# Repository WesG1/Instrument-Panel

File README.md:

# Instrument Panel
Description:
    Digital custom 65 mustang modern insturment panel. Uses six servo motors along with RGB LEDs to display gauge information. Controlled by an ESP32-s2. Motors and warning lights are interfaced through I2C protocall using a PCA9685 controller. Odometer and tripmeter are displayed on an I2C LCD. 
    
    Odo and trip values are stored in an EEPROM chip with a wear leveling algorithm. Odometer value is also stored in a second backup EEPROM. At startup the values of both EEPROMs are read, and if they are different the higher value is set as the current mileage. At shutdown the last stored value and current value for the mileage are compared and the current value is only stored if it is higher than the saved value.

    Each servo motor (execpt voltage) has a deticated sensor. The signals from the oil, temp, and fuel sensors are passed through a calibrated voltage divider to drop them to a level safe for the ESP32 to read. Speed and tach are a digital pulse and are passed through a logic shifter. Voltage is derived by an algorithm and read by a voltage divider from the dash power supply. Volts, oil, temp, and fuel have accompanying warning lights that turn red if the value goes out of a safe range, are off if the value is normal and the headlights are off, and white if the values is normal and the headlights are on. Temp has additionally will turn yellow if the value is too low.

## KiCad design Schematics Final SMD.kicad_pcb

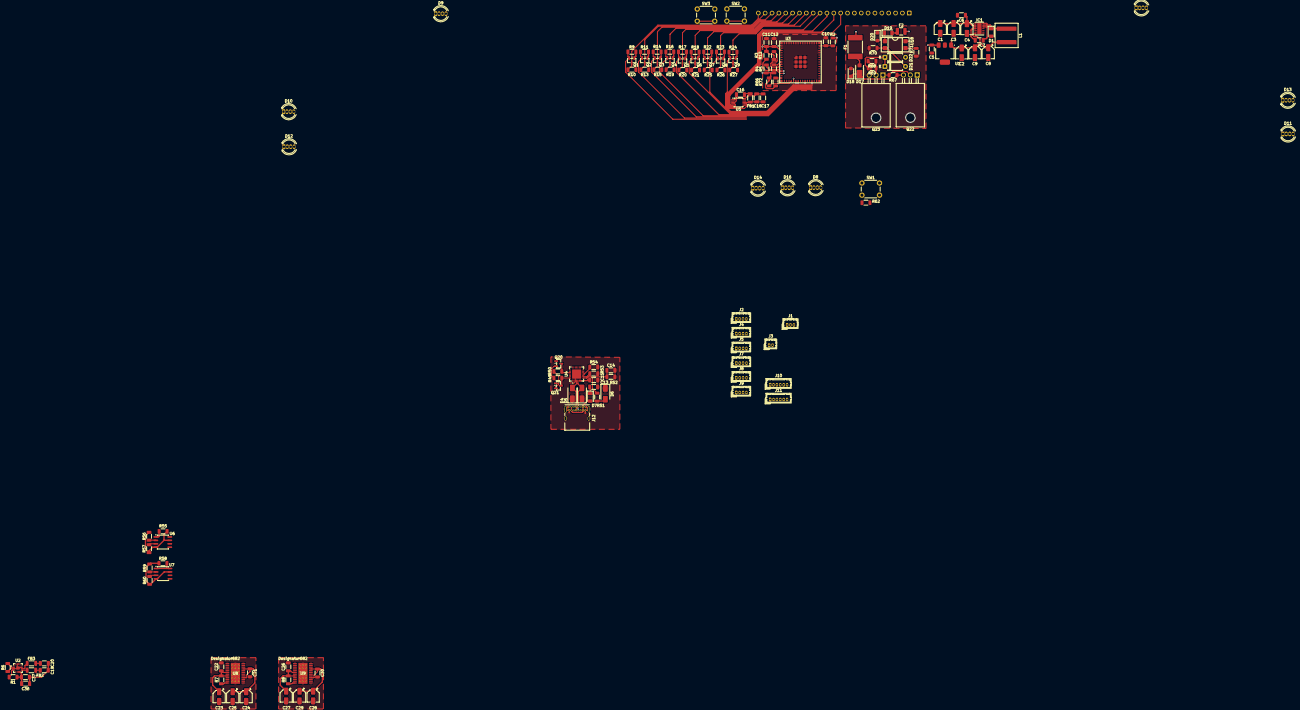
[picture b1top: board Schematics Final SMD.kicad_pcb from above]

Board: 4 copper layers, 144 parts (1 on the bottom side), 116 nets.

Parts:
C1, C3, C4: 15uF; CP_Elec_4x4.5
C2: 0.33u; CP_Elec_4x4.5
C5, C12, C21, C22, C26, C30: 0.1u; C_1206_3216Metric
C6: 0.47uF; C_1206_3216Metric
C7: 0.01uF; C_1206_3216Metric
C8, C9: 180uF; CP_Elec_4x4.5
C10, C14: 1u; C_1206_3216Metric
C11, C13, C15: 10u; C_1206_3216Metric
C16, C18, C36: 10uF; C_1206_3216Metric
C17, C37: 0.1uF; C_1206_3216Metric
C19, C20: 220pF; C_1206_3216Metric
C23, C27: 1u; CP_Elec_4x4.5
C24, C25, C28, C29: 10u; CP_Elec_4x4.5
D1: D_Schottky; D_1206_3216Metric
D4, D5, D6: SMAJ5.0CA; D_SMA
D7: 1N5819; D_1206_3216Metric
D8: Low_Beam_LED; LED_D5.0mm-4_RGB
D9: Left_Turn_LED; LED_D5.0mm-4_RGB
D10: Oil_LED; LED_D5.0mm-4_RGB
D11: Temp_LED; LED_D5.0mm-4_RGB
D12: Fuel_LED; LED_D5.0mm-4_RGB
D13: Batt_LED; LED_D5.0mm-4_RGB
D14: HIgh_Beam_LED; LED_D5.0mm-4_RGB
D15: Right_Turn_LED; LED_D5.0mm-4_RGB
D16: Brake_LED; LED_D5.0mm-4_RGB
D17: D_Schottky; Vishay_SMPA
D18, D20: SMF18A; D_SMF
D19: 1N914; D_1206_3216Metric
D21, D22: D; D_A-405_P7.62mm_Horizontal
F1: Polyfuse; Fuse_2920_7451Metric_Pad2.10x5.45mm_HandSolder
F2: Polyfuse; Fuse_1210_3225Metric
FB1, FB2, FB3: FerriteBead_Small; L_1206_3216Metric
IC1: LM2678SD-5.0_NOPB; VSON-14-1EP_3x4.45mm_P0.65mm_EP1.6x4.2mm
J1: Conn_01x03_Socket; Hirose_DF13-03P-1.25DSA_1x03_P1.25mm_Vertical
J2, J4, J5, J7, J8, J9: Conn_01x04_Socket; Hirose_DF13-04P-1.25DSA_1x04_P1.25mm_Vertical
J3: Conn_01x02_Socket; Hirose_DF13-02P-1.25DSA_1x02_P1.25mm_Vertical
J6: Conn_01x23_Socket; Molex_SL_171971-0023_1x23_P2.54mm_Vertical
J10, J11: Conn_01x06_Socket; Hirose_DF13-06P-1.25DSA_1x06_P1.25mm_Vertical
J12: USB_C_Receptacle_USB2.0_14P; USB_C_Receptacle_GCT_USB4085
L1: 22uH; L_Wuerth_XHMI-8080
Q1, Q2, Q3, Q4, Q5, Q6, Q7, Q8, Q9: BSS138; SOT-23
Q20, Q21: NPN; SOT-23
Q22: PMOS; TO-220F-3_Horizontal_TabDown
Q23: NMOS; TO-220F-3_Horizontal_TabDown
R1: 1M; R_1206_3216Metric
R2, R49, R50, R55, R56, R57, R58, R59, R60, R62: 10K; R_1206_3216Metric
R3, R4, R5, R7, R8, R9, R10, R11, R12, R13, R14, R15, R16, R17, R18, R19, R20, R21, R22, R23, R24, R25, R26, R27, R66, R67, R71, R72: 10k; R_1206_3216Metric
R6: 100K; R_1206_3216Metric
R51: 22.1K; R_1206_3216Metric
R52: 47.5K; R_1206_3216Metric
R53: 1K; R_1206_3216Metric
R54: 11K; R_1206_3216Metric
R68: 47k; R_1206_3216Metric
R69, R70: 1k; R_1206_3216Metric
SW1, SW2, SW3: SW_Push; SW_PUSH_6mm_H8mm
U1: UA78M33QDCYRQ1; SOT-223-3_TabPin2
U2: MAX98357A; TQFN-16-1EP_3x3mm_P0.5mm_EP1.23x1.23mm
U3: ESP32-S2-MINI-2U-N4; XCVR_ESP32-S2-MINI-2U-N4
U4: CP2102N-Axx-xQFN28; QFN-28-1EP_5x5mm_P0.5mm_EP3.35x3.35mm
U5: ADS1015IDGS; TSSOP-10_3x3mm_P0.5mm
U6, U7: 24C02Cx-x-SN; SO-8_3.9x4.9mm_P1.27mm
U8, U9: DRV8912QPWPRQ1; PWP0024N_N
U18: SFH617A-1; DIP-4_W7.62mm_SMDSocket_SmallPads

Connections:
+3.3V: C5.1, C11.1, C12.1, C15.1, C22.1, C23.1, C26.1, C27.1, J6.4, J10.2, J11.2, Q1.1 (G), Q2.1 (G), Q3.1 (G), Q4.1 (G), Q5.1 (G), Q6.1 (G), Q7.1 (G), Q8.1 (G), Q9.1 (G), R2.1, R3.1, R4.1, R5.1, R7.1, R8.1, R9.1, R11.1, R12.1, R14.1, R16.1, R17.1, R18.1, R22.1, R23.1, R24.1, R58.2, R66.1, R72.1, SW1.1, U1.3 (OUT), U3.3 (3V3), U4.6 (VDD), U4.7 (VREGIN), U6.8 (VCC), U7.1 (A0), U7.8 (VCC), U8.6 (VDD), U8.8 (SLEEP_N), U9.6 (VDD), U9.8 (SLEEP_N), U18.4
+5V: C2.1, C8.1, C9.1, C13.1, C16.1, C21.1, C24.1, C25.1, C28.1, C29.1, C30.1, C36.1, C37.1, D7.1 (K), D8.3 (VDD), D9.3 (VDD), D10.3 (VDD), D11.3 (VDD), D12.3 (VDD), D13.3 (VDD), D14.3 (VDD), D15.3 (VDD), D16.3 (VDD), FB1.1, IC1.7 (FB), J1.3, J6.7, L1.2, R1.2, R20.1, U1.1 (IN), U2.7 (VDD), U2.8 (VDD), U8.16 (VM), U8.21 (VM), U9.16 (VM), U9.21 (VM)
+BATT: F1.2, J6.9
+VDC: F2.2, J6.10
/Trip Reset: R62.1, SW1.2, U3.25 (IO21)
/USB and Power/Constant Power: D17.1 (K), D18.1 (A1), Q22.3 (S), R67.1
/USB and Power/DTR: Q21.3 (E), R49.1, U4.28 (~DTR)
/USB and Power/RTS: Q20.3 (E), R50.1, U4.24 (~RTS)
/USB and Power/Switched Power: D19.1 (K), D20.1 (A1), U18.1
/USB and Power/USB_D_N: D5.2 (A2), J12.A7 (D-), J12.B7 (D-), U4.5 (D-)
/USB and Power/USB_D_P: D4.2 (A2), J12.A6 (D+), J12.B6 (D+), U4.4 (D+)
BCLK: U2.16 (BCLK), U3.17 (IO13)
Backlight_Strip: D15.1 (DO), J1.2
Batt Out 1: J8.4, U9.3 (OUT5)
Batt Out 2: J8.3, U9.10 (OUT6)
Batt Out 3: J8.2, U9.4 (OUT7)
Batt Out 4: J8.1, U9.22 (OUT8)
Batt_In: J6.11, U5.5 (AIN1)
Brake_Adjusted: Q2.2 (S), R11.2, U3.31 (IO35)
Brake_In: J6.22, Q2.3 (D), R13.2
CL: J10.3, J11.3, U3.11 (IO7), U8.20 (SCLK), U9.20 (SCLK)
CS0: J11.5, R12.2, U3.9 (IO5)
CS1: J10.5, R5.2, U3.8 (IO4)
CS2: R66.2, U3.19 (IO15), U8.19 (SCS_N)
CS3: R72.2, U3.15 (IO11), U9.19 (SCS_N)
Chip_PU: C10.1, Q20.1 (C), R2.2, SW2.2, U3.45 (EN)
DA: J10.4, J11.4, U3.7 (IO3), U8.5 (SDI), U9.5 (SDI)
DC: J10.6, J11.6, U3.6 (IO2)
DIN: U2.1 (DIN), U3.28 (IO33)
Echo_Adjusted: Q5.2 (S), R17.2, U3.34 (IO38)
Echo_In: J6.19, Q5.3 (D), R20.2
Fuel Out 1: J4.4, U8.3 (OUT5)
Fuel Out 2: J4.3, U8.10 (OUT6)
Fuel Out 3: J4.2, U8.4 (OUT7)
Fuel Out 4: J4.1, U8.22 (OUT8)
Fuel_In: J6.13, U5.6 (AIN2)
GND: C1.2, C2.2, C3.2, C4.2, C5.2, C6.2, C8.2, C9.2, C10.2, C11.2, C12.2, C13.2, C14.2, C15.2, C16.2, C17.2, C18.2, C19.2, C20.2, C21.2, C22.2, C23.2, C24.2, C25.2, C26.2, C27.2, C28.2, C29.2, C30.2, C36.2, C37.2, D1.2 (A), D4.1 (A1), D5.1 (A1), D6.1 (A1), D8.2 (GND), D9.2 (GND), D10.2 (GND), D11.2 (GND), D12.2 (GND), D13.2 (GND), D14.2 (GND), D15.2 (GND), D16.2 (GND), D18.2 (A2), D20.2 (A2), IC1.9 (GND), J1.1, J6.1, J6.5, J6.8, J10.1, J11.1, J12.A1 (GND), J12.A12 (GND), J12.B1 (GND), J12.B12 (GND), J12.SH (SHIELD), Q23.3 (S), R6.2, R52.2, R53.2, R54.2, R55.1, R56.1, R57.1, R58.1, R59.1, R60.1, R62.2, R68.2, R70.2, R71.1, SW2.1, SW3.1, U1.2 (GND), U2.3 (GND), U2.11 (GND), U2.15 (GND), U2.17 (PAD), U3.1 (GND1), U3.2 (GND1__1), U3.30 (GND1__2), U3.42 (GND1__3), U3.43 (GND1__4), U3.46 (GND1__5), U3.47 (GND1__6), U3.48 (GND1__7), U3.49 (GND1__8), U3.50 (GND1__9), U3.51 (GND1__10), U3.52 (GND1__11), U3.53 (GND1__12), U3.54 (GND1__13), U3.55 (GND1__14), U3.56 (GND2), U3.57 (GND2__1), U3.58 (GND2__2), U3.59 (GND2__3), U3.60 (GND2__4), U3.61_1 (GND2__5), U3.61_2 (GND2__6), U3.61_3 (GND2__7), U3.61_4 (GND2__8), U3.61_5 (GND2__9), U3.61_6 (GND2__10), U3.61_7 (GND2__11), U3.61_8 (GND2__12), U3.61_9 (GND2__13), U3.62 (GND2__14), U3.63 (GND3), U3.64 (GND3__1), U3.65 (GND3__2), U4.3 (GND), U4.29 (GND), U5.1 (ADDR), U5.3 (GND), U6.4 (GND), U6.7 (WP), U7.4 (GND), U7.7 (WP), U8.1 (GND), U8.13 (GND), U8.24 (GND), U8.25 (GND), U9.1 (GND), U9.13 (GND), U9.24 (GND), U9.25 (GND)
GPIO0: Q21.1 (C), SW3.2, U3.4 (IO0)
Hazard_Adjusted: Q6.2 (S), R18.2, U3.35 (IO39)
Hazard_In: J6.18, Q6.3 (D), R21.2
Headlights_High_Adjusted: Q1.2 (S), R9.2, U3.29 (IO34)
Headlights_High_In: J6.23, Q1.3 (D), R10.2
Headlights_Low_Adjusted: Q7.2 (S), R22.2, U3.36 (IO40)
Headlights_Low_In: J6.17, Q7.3 (D), R25.2
Ignition_Sensor: R71.2, U3.22 (IO18), U18.3
LED_Data_Out: D9.4 (DI), U3.5 (IO1)
LRCLK: U2.14 (LRCLK), U3.18 (IO14)
Left_Turn_Adjusted: Q4.2 (S), R16.2, U3.33 (IO37)
Left_Turn_In: J6.20, Q4.3 (D), R19.2
unnamed: C7.2, D1.1 (K), IC1.12 (SWITCH_OUTPUT_1), IC1.13 (SWITCH_OUTPUT_2), IC1.14 (SWITCH_OUTPUT_3), L1.1
unnamed: D9.1 (DO), D10.4 (DI)
unnamed: D10.1 (DO), D12.4 (DI)
unnamed: D8.1 (DO), D11.4 (DI)
unnamed: D11.1 (DO), D13.4 (DI)
unnamed: D12.1 (DO), D14.4 (DI)
unnamed: D13.1 (DO), D15.4 (DI)
unnamed: D14.1 (DO), D16.4 (DI)
unnamed: D8.4 (DI), D16.1 (DO)
unnamed: D17.2 (A), F1.1
unnamed: D19.2 (A), F2.1
unnamed: D21.2 (A), R70.1, U18.2
unnamed: D21.1 (K), D22.1 (K), R69.2
unnamed: C7.1, IC1.4 (CB)
unnamed: C19.1, FB2.2, J3.1
unnamed: C20.1, FB3.2, J3.2
unnamed: Q20.2 (B), R49.2
unnamed: Q21.2 (B), R50.2
unnamed: Q22.2 (G), Q23.1 (D), R67.2
unnamed: Q23.2 (G), R68.1, R69.1
unnamed: R6.1, U2.2 (GAIN_SLOT)
unnamed: FB3.1, U2.10 (OUTN)
unnamed: FB2.1, U2.9 (OUTP)
unnamed: C14.1, R51.1, R52.1, U4.8 (VBUS)
unnamed: R53.1, U4.9 (~RST)
unnamed: R54.1, U4.11 (~SUSPEND)
unnamed: R55.2, U6.1 (A0)
unnamed: R56.2, U6.2 (A1)
unnamed: R57.2, U6.3 (A2)
unnamed: R59.2, U7.2 (A1)
unnamed: R60.2, U7.3 (A2)
unnamed: R7.2, U8.12 (FAULT_N)
unnamed: R8.2, U9.12 (FAULT_N)
Oil Out 1: J2.4, U8.2 (OUT1)
Oil Out 2: J2.3, U8.23 (OUT2)
Oil Out 3: J2.2, U8.14 (OUT3)
Oil Out 4: J2.1, U8.11 (OUT4)
Oil_In: J6.14, U5.7 (AIN3)
Power_Off: D22.2 (A), U3.21 (IO17)
Right_Turn_Adjusted: Q3.2 (S), R14.2, U3.32 (IO36)
Right_Turn_In: J6.21, Q3.3 (D), R15.2
SCL: J6.2, R3.2, U3.13 (IO9), U5.10 (SCL), U6.6 (SCL), U7.6 (SCL)
SDA: J6.3, R4.2, U3.12 (IO8), U5.9 (SDA), U6.5 (SDA), U7.5 (SDA)
SD_MODE: R1.1, U2.4 (~SD_MODE), U3.16 (IO12)
Spd Out 1: J5.4, U8.9 (OUT9)
Spd Out 2: J5.3, U8.15 (OUT10)
Spd Out 3: J5.2, U8.17 (OUT11)
Spd Out 4: J5.1, U8.18 (OUT12)
Speed_Adjusted: Q8.2 (S), R23.2, U3.37 (IO41)
Speed_In: J6.16, Q8.3 (D), R26.2
Tach Out 1: J7.4, U9.2 (OUT1)
Tach Out 2: J7.3, U9.23 (OUT2)
Tach Out 3: J7.2, U9.14 (OUT3)
Tach Out 4: J7.1, U9.11 (OUT4)
Tach_Adjusted: Q9.2 (S), R24.2, U3.38 (IO42)
Tach_In: J6.15, Q9.3 (D), R27.2
Temp Out 1: J9.4, U9.9 (OUT9)
Temp Out 2: J9.3, U9.15 (OUT10)
Temp Out 3: J9.2, U9.17 (OUT11)
Temp Out 4: J9.1, U9.18 (OUT12)
Temp_In: J6.12, U5.4 (AIN0)
Trigger: J6.6, U3.20 (IO16)
U0RXT: U3.40 (IO44/RXD0), U4.26 (TXD)
U0TXD: U3.39 (IO43/TXD0), U4.25 (RXD)
VAA: C1.1, C3.1, C4.1, C6.1, IC1.2 (INPUT_1), IC1.3 (INPUT_2), Q22.1 (D), R10.1, R13.1, R15.1, R19.1, R21.1, R25.1, R26.1, R27.1
VBUS: D6.2 (A2), D7.2 (A), J12.A4 (VBUS), J12.A9 (VBUS), J12.B4 (VBUS), J12.B9 (VBUS), R51.2
VDDA: C17.1, C18.1, FB1.2, U5.8 (VDD)

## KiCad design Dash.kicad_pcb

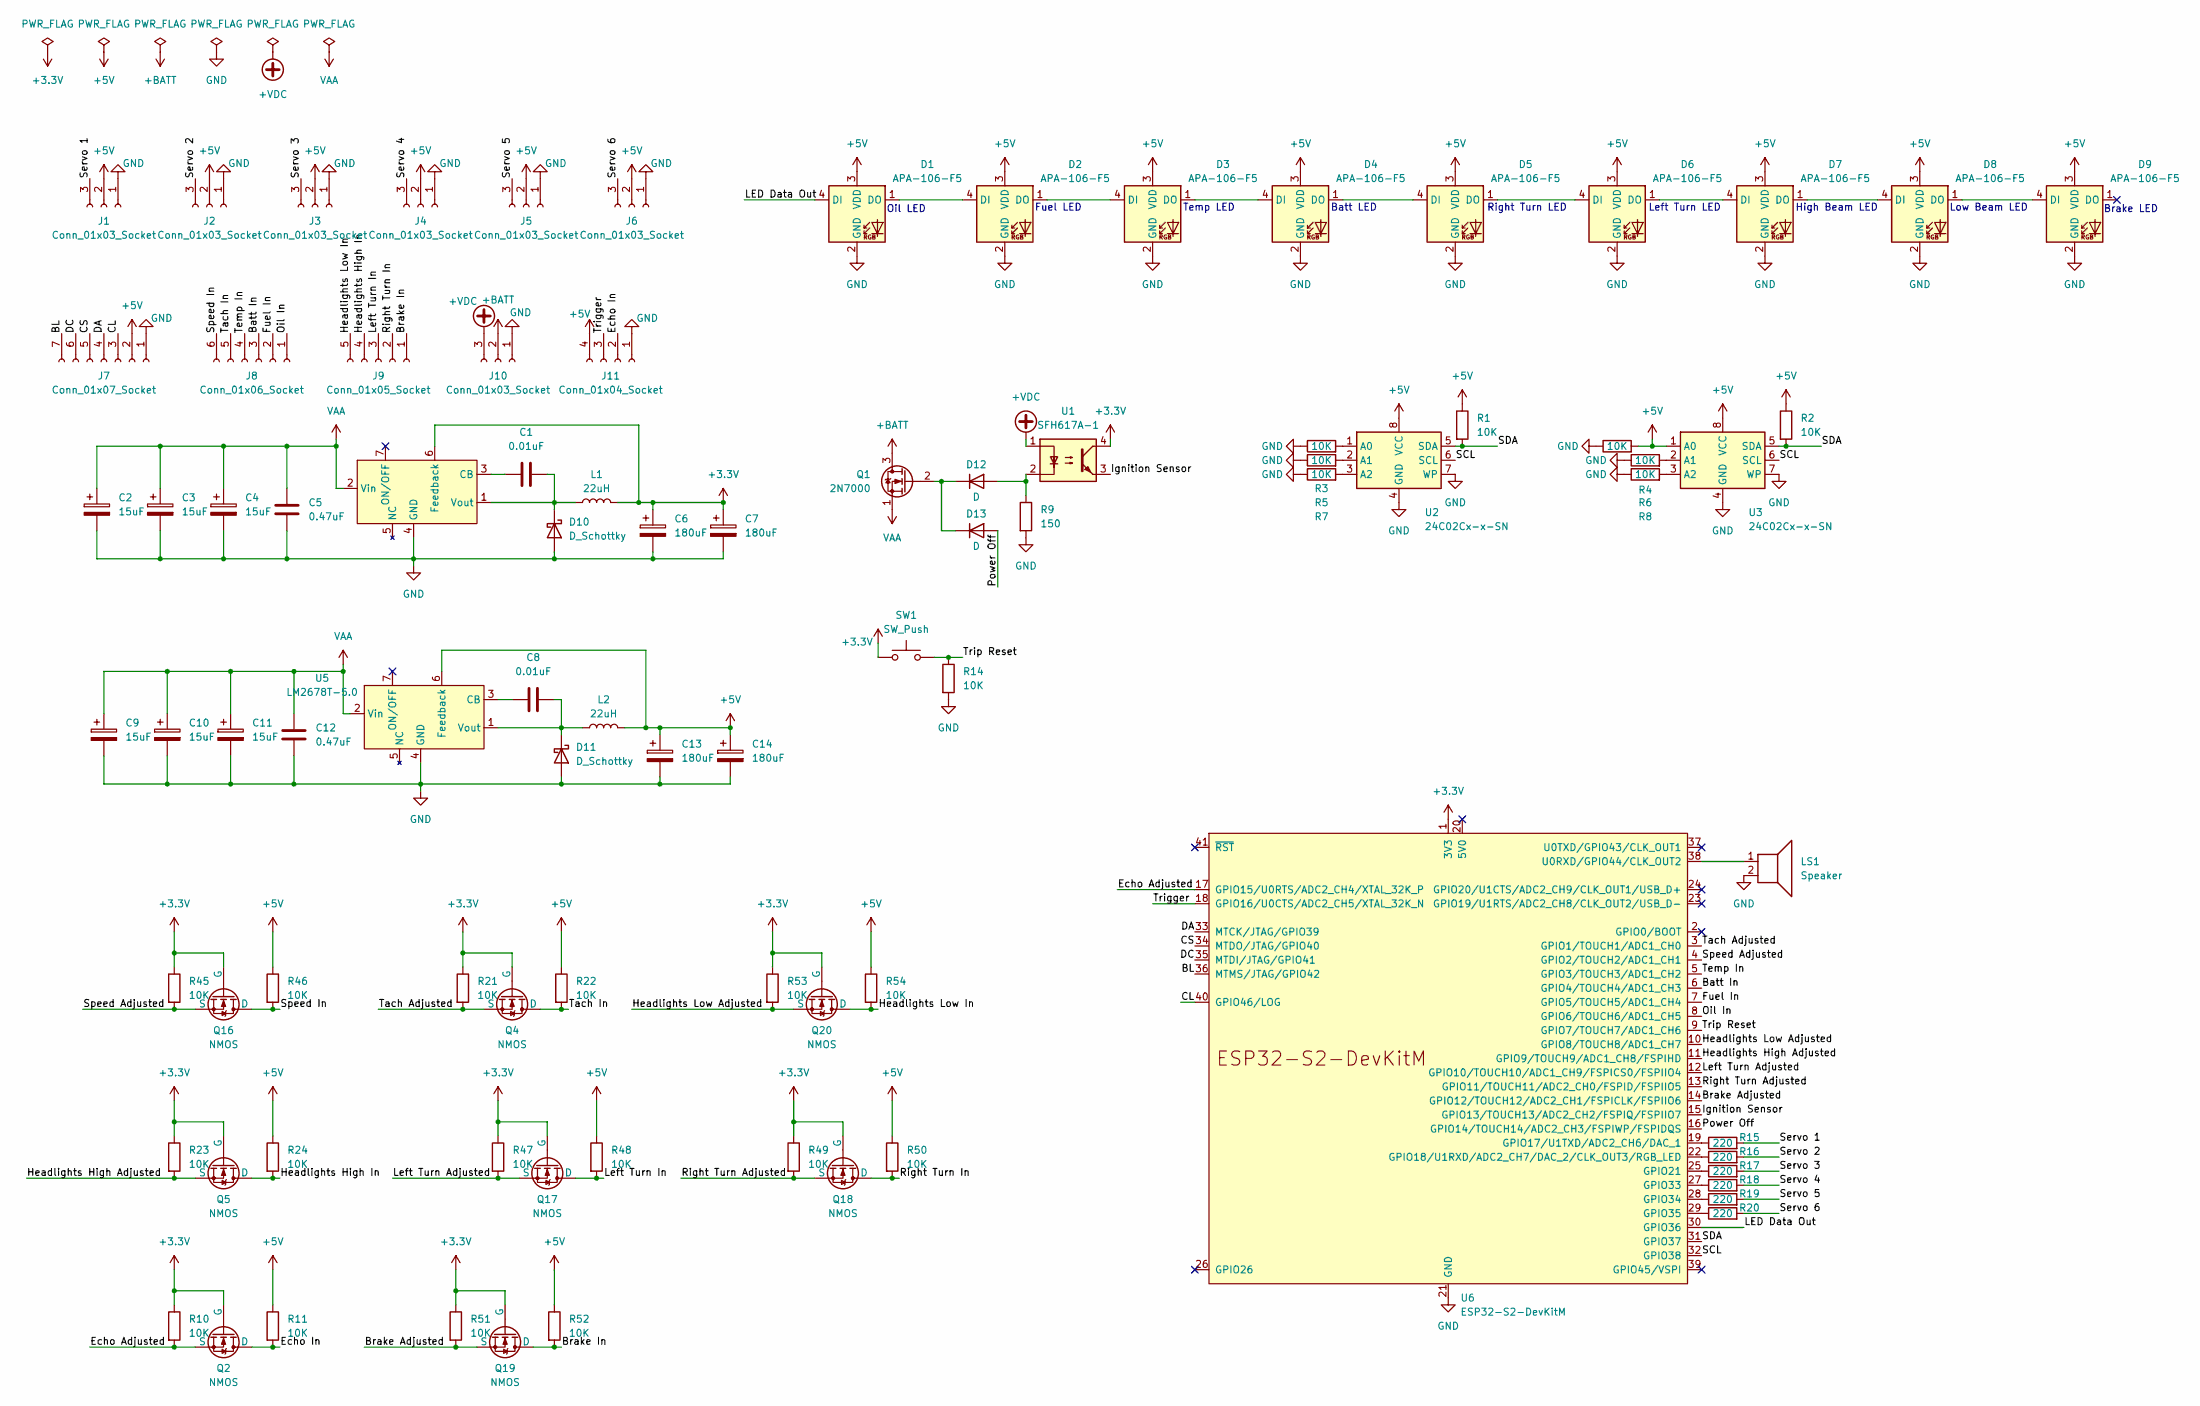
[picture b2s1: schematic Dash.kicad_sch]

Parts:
C1, C8: 0.01uF; C_Disc_D3.0mm_W1.6mm_P2.50mm
C2, C3, C4, C9, C10, C11: 15uF; CP_Radial_D5.0mm_P2.50mm
C5, C12: 0.47uF; C_Disc_D3.0mm_W1.6mm_P2.50mm
C6, C7, C13, C14: 180uF; CP_Radial_D5.0mm_P2.50mm
D1, D2, D3, D4, D5, D6, D7, D8, D9: APA-106-F5; LED_D5.0mm-4_RGB
D10, D11: D_Schottky; D_A-405_P7.62mm_Horizontal
D12, D13: D; D_A-405_P7.62mm_Horizontal
J1, J2, J3, J4, J5, J6, J10: Conn_01x03_Socket; Molex_KK-396_A-41791-0003_1x03_P3.96mm_Vertical
J7: Conn_01x07_Socket; Molex_KK-396_5273-07A_1x07_P3.96mm_Vertical
J8: Conn_01x06_Socket; Molex_KK-396_5273-06A_1x06_P3.96mm_Vertical
J9: Conn_01x05_Socket; Molex_KK-396_5273-05A_1x05_P3.96mm_Vertical
J11: Conn_01x04_Socket; Molex_KK-396_5273-04A_1x04_P3.96mm_Vertical
L1, L2: 22uH; L_Radial_D9.5mm_P5.00mm_Fastron_07HVP
LS1: Speaker; Molex_KK-396_5273-02A_1x02_P3.96mm_Vertical
Q1: 2N7000; TO-92_Inline
Q2, Q4, Q5, Q16, Q17, Q18, Q19, Q20: NMOS; TO-92_Inline
R1, R2, R3, R4, R5, R6, R7, R8, R10, R11, R14, R21, R22, R23, R24, R45, R46, R47, R48, R49, R50, R51, R52, R53, R54: 10K; R_Axial_DIN0207_L6.3mm_D2.5mm_P10.16mm_Horizontal
R9: 150; R_Axial_DIN0207_L6.3mm_D2.5mm_P10.16mm_Horizontal
R15, R16, R17, R18, R19, R20: 220; R_Axial_DIN0207_L6.3mm_D2.5mm_P10.16mm_Horizontal
SW1: SW_Push; SW_PUSH_6mm_H8mm
U1: SFH617A-1; DIP-4_W7.62mm
U2, U3: 24C02Cx-x-SN; SOIC-8_3.9x4.9mm_P1.27mm
U4: LM2678T-3.3; TO-220-7_P2.54x3.7mm_StaggerOdd_Lead3.8mm_Vertical
U5: LM2678T-5.0; TO-220-7_P2.54x3.7mm_StaggerOdd_Lead3.8mm_Vertical
U6: ESP32-S2-DevKitM

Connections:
+3.3V: C6.1, C7.1, L1.2, Q2.2 (G), Q4.2 (G), Q5.2 (G), Q16.2 (G), Q17.2 (G), Q18.2 (G), Q19.2 (G), Q20.2 (G), R10.1, R21.1, R23.1, R45.1, R47.1, R49.1, R51.1, R53.1, SW1.1, U1.4, U4.6 (Feedback), U6.1 (3V3)
+5V: C13.1, C14.1, D1.3 (VDD), D2.3 (VDD), D3.3 (VDD), D4.3 (VDD), D5.3 (VDD), D6.3 (VDD), D7.3 (VDD), D8.3 (VDD), D9.3 (VDD), J1.2, J2.2, J3.2, J4.2, J5.2, J6.2, J7.2, J11.4, L2.2, R1.1, R2.1, R4.2, R11.1, R22.1, R24.1, R46.1, R48.1, R50.1, R52.1, R54.1, U2.8 (VCC), U3.1 (A0), U3.8 (VCC), U5.6 (Feedback)
+BATT: J10.2, Q1.3 (D)
+VDC: J10.3, U1.1
/BL: J7.7, U6.36 (MTMS/JTAG/GPIO42)
/Batt In: J8.3, U6.6 (GPIO4/TOUCH4/ADC1_CH3)
/Brake Adjusted: Q19.3 (S), R51.2, U6.14 (GPIO12/TOUCH12/ADC2_CH1/FSPICLK/FSPIIO6)
/Brake In: J9.1, Q19.1 (D), R52.2
/CL: J7.3, U6.40 (GPIO46/LOG)
/CS: J7.5, U6.34 (MTDO/JTAG/GPIO40)
/DA: J7.4, U6.33 (MTCK/JTAG/GPIO39)
/DC: J7.6, U6.35 (MTDI/JTAG/GPIO41)
/Echo Adjusted: Q2.3 (S), R10.2, U6.17 (GPIO15/U0RTS/ADC2_CH4/XTAL_32K_P)
/Echo In: J11.2, Q2.1 (D), R11.2
/Fuel In: J8.2, U6.7 (GPIO5/TOUCH5/ADC1_CH4)
/Headlights High Adjusted: Q5.3 (S), R23.2, U6.11 (GPIO9/TOUCH9/ADC1_CH8/FSPIHD)
/Headlights High In: J9.4, Q5.1 (D), R24.2
/Headlights Low Adjusted: Q20.3 (S), R53.2, U6.10 (GPIO8/TOUCH8/ADC1_CH7)
/Headlights Low In: J9.5, Q20.1 (D), R54.2
/Ignition Sensor: U1.3, U6.15 (GPIO13/TOUCH13/ADC2_CH2/FSPIQ/FSPIIO7)
/LED Data Out: D1.4 (DI), U6.30 (GPIO36)
/Left Turn Adjusted: Q17.3 (S), R47.2, U6.12 (GPIO10/TOUCH10/ADC1_CH9/FSPICS0/FSPIIO4)
/Left Turn In: J9.3, Q17.1 (D), R48.2
/Oil In: J8.1, U6.8 (GPIO6/TOUCH6/ADC1_CH5)
/Power Off: D13.2 (A), U6.16 (GPIO14/TOUCH14/ADC2_CH3/FSPIWP/FSPIDQS)
/Right Turn Adjusted: Q18.3 (S), R49.2, U6.13 (GPIO11/TOUCH11/ADC2_CH0/FSPID/FSPIIO5)
/Right Turn In: J9.2, Q18.1 (D), R50.2
/SCL: U2.6 (SCL), U3.6 (SCL), U6.32 (GPIO38)
/SDA: R1.2, R2.2, U2.5 (SDA), U3.5 (SDA), U6.31 (GPIO37)
/Servo 1: J1.3, R15.2
/Servo 2: J2.3, R16.2
/Servo 3: J3.3, R17.2
/Servo 4: J4.3, R18.2
/Servo 5: J5.3, R19.2
/Servo 6: J6.3, R20.2
/Speed Adjusted: Q16.3 (S), R45.2, U6.4 (GPIO2/TOUCH2/ADC1_CH1)
/Speed In: J8.6, Q16.1 (D), R46.2
/Tach Adjusted: Q4.3 (S), R21.2, U6.3 (GPIO1/TOUCH1/ADC1_CH0)
/Tach In: J8.5, Q4.1 (D), R22.2
/Temp In: J8.4, U6.5 (GPIO3/TOUCH3/ADC1_CH2)
/Trigger: J11.3, U6.18 (GPIO16/U0CTS/ADC2_CH5/XTAL_32K_N)
/Trip Reset: R14.1, SW1.2, U6.9 (GPIO7/TOUCH7/ADC1_CH6)
GND: C2.2, C3.2, C4.2, C5.2, C6.2, C7.2, C9.2, C10.2, C11.2, C12.2, C13.2, C14.2, D1.2 (GND), D2.2 (GND), D3.2 (GND), D4.2 (GND), D5.2 (GND), D6.2 (GND), D7.2 (GND), D8.2 (GND), D9.2 (GND), D10.2 (A), D11.2 (A), J1.1, J2.1, J3.1, J4.1, J5.1, J6.1, J7.1, J10.1, J11.1, LS1.2, R3.1, R4.1, R5.1, R6.1, R7.1, R8.1, R9.2, R14.2, U2.4 (GND), U2.7 (WP), U3.4 (GND), U3.7 (WP), U4.4 (GND), U5.4 (GND), U6.21 (GND), U6.42 (GND)
unnamed: D1.1 (DO), D2.4 (DI)
unnamed: D2.1 (DO), D3.4 (DI)
unnamed: D3.1 (DO), D4.4 (DI)
unnamed: D4.1 (DO), D5.4 (DI)
unnamed: D5.1 (DO), D6.4 (DI)
unnamed: D6.1 (DO), D7.4 (DI)
unnamed: D7.1 (DO), D8.4 (DI)
unnamed: D8.1 (DO), D9.4 (DI)
unnamed: C1.2, D10.1 (K), L1.1, U4.1 (Vout)
unnamed: C8.2, D11.1 (K), L2.1, U5.1 (Vout)
unnamed: D12.2 (A), R9.1, U1.2
unnamed: D12.1 (K), D13.1 (K), Q1.2 (G)
unnamed: R3.2, U2.1 (A0)
unnamed: R5.2, U2.2 (A1)
unnamed: R7.2, U2.3 (A2)
unnamed: R6.2, U3.2 (A1)
unnamed: R8.2, U3.3 (A2)
unnamed: C1.1, U4.3 (CB)
unnamed: C8.1, U5.3 (CB)
unnamed: R15.1, U6.19 (GPIO17/U1TXD/ADC2_CH6/DAC_1)
unnamed: R16.1, U6.22 (GPIO18/U1RXD/ADC2_CH7/DAC_2/CLK_OUT3/RG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)
unnamed: R17.1, U6.25 (GPIO21)
unnamed: R18.1, U6.27 (GPIO33)
unnamed: R19.1, U6.28 (GPIO34)
unnamed: R20.1, U6.29 (GPIO35)
unnamed: LS1.1, U6.38 (U0RXD/GPIO44/CLK_OUT2)
VAA: C2.1, C3.1, C4.1, C5.1, C9.1, C10.1, C11.1, C12.1, Q1.1 (S), U4.2 (Vin), U5.2 (Vin)

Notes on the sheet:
Low Beam LED
High Beam LED
Fuel LED
Oil LED
Temp LED
Batt LED
Left Turn LED
Right Turn LED
Brake LED

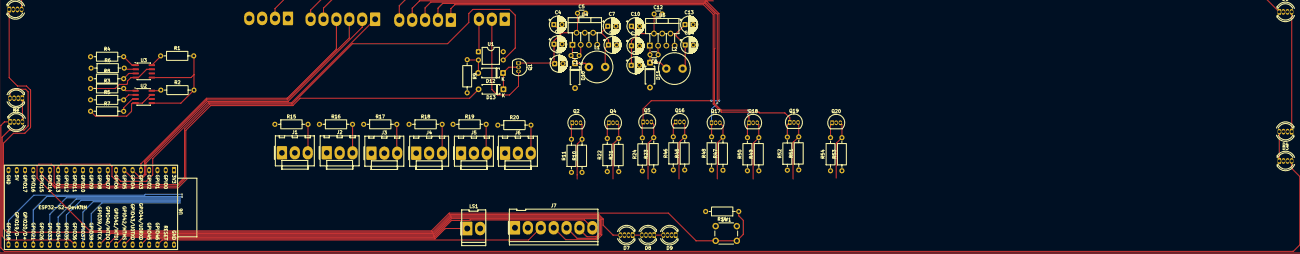
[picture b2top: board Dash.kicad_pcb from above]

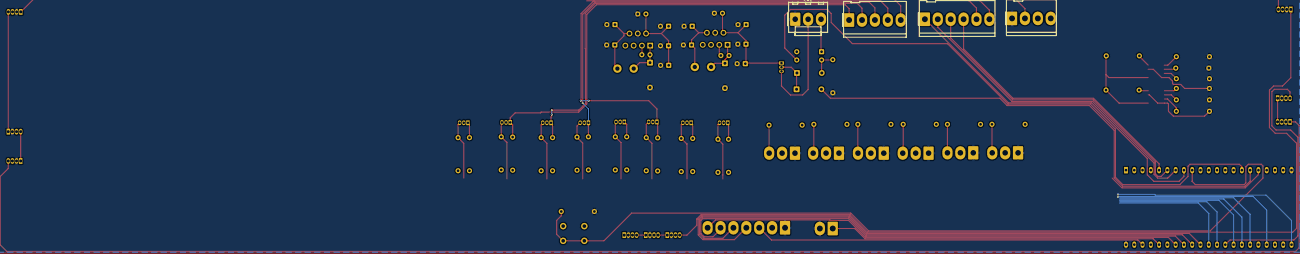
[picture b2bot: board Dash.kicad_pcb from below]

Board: 4 copper layers, 89 parts (4 on the bottom side), 70 nets.

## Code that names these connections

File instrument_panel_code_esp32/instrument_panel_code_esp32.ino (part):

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// ─────────────────────────────────────────────
//  STEPPER MOTOR DEFINITIONS (6x 28BYJ-48, one L293D each)
//
//  Signal chain:  ESP32 SPI (MOSI=DA/GPIO3, SCK=CL/GPIO7)
//                   -> U7 -> U8 -> U9  (3x 74HC595 daisy-chained via QH'->SER)
//                   -> 24 outputs -> 6 x L293D (4 inputs each) -> 6 x 28BYJ-48
//  The '595 RCLK (latch) pins are all tied to the CS2 net = GPIO15.
//  Because the shift registers share MOSI/SCK with the TFT displays, every
//  update shifts out all 24 bits in ONE SPI transaction and latches before
//  the transaction ends, so TFT traffic can never reach the outputs.
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#define NUM_STEPPERS        6

// Latch pin for all three 74HC595s (CS2 net -> RCLK). Pulsed HIGH to
// transfer the shifted bits to the outputs. (GPIO15 was a servo pin before.)
#define STEPPER_LATCH_PIN   15

// Optional: GPIO driving the '595 /OE pins. As drawn in the schematic, /OE
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
// ─── POWER LATCH ───
#define IGNITION_PIN          18    // input from optocoupler: HIGH = key on
#define POWER_OFF_PIN         17    // output: HIGH holds the power latch on
#define SHUTDOWN_DELAY_MS     3000  // placeholder for real shutdown work
#define IGNITION_DEBOUNCE_MS  100   // ignore brief dips (e.g. cranking)

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      }

      if (!aborted) {
        digitalWrite(POWER_OFF_PIN, LOW);   // release the latch; power should drop
        vTaskDelay(pdMS_TO_TICKS(500));
        // Still running means the key came back on at the last moment.
        digitalWrite(POWER_OFF_PIN, HIGH);  // re-latch
      }
      lowMs = 0;
    }
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
  // ── Stepper drivers (74HC595 chain -> L293D -> 28BYJ-48) ──
  // The shift registers sit on the same SPI bus as the TFTs (tftSPI.begin()
  // has already run above), with CS2 / GPIO15 acting as their latch (RCLK).

  pinMode(IGNITION_PIN, INPUT);        // optocoupler drives it, R63 pulls it down
  pinMode(POWER_OFF_PIN, OUTPUT);
  digitalWrite(POWER_OFF_PIN, HIGH);   // latch power on  

  Serial.println("Init stepper shift registers...");

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
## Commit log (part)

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2026-01-27 Create instrument_panel_code_esp32.ino
    Add project code
2026-01-27 Created schematic branch
    added initial KiCAD schematic and PCB files
2026-02-03 Initial commit for test bench
    A separate circuit to generate sensor signals and light switches
2026-02-10 defined pins
    Added pins to detect headlight activation and pins to detect switched power to unit and control constant power
2026-02-12 Update instrument_panel_code_esp32.ino
    Added comments to clarify parts used and the reserved addresses for those parts. And defined second second i2c driver for LEDs
2026-02-17 Updated schematics
    Added power, logic conversion, eeprom, and other components
2026-02-18 Uploaded correct versions
    uploading correct versions of schematics
2026-02-24 added components
    added power flags, servo connectors, optocoupler, and mosfet
2026-02-25 update
    added more parts to schematic
2026-02-25 update
    added parts to schematic, added pin definitions in code
2026-03-04 Removed PCA chips
    removed pca chips, added additional parts, moved leds to single bus
2026-03-04 update 3/3/26
2026-03-04 Added note, removed extra files
    Added note to change code to reflect hard changes. Removed extra PCB and schematic file
2026-03-04 Second Update
    Added inputs for turn and brake lights, fixed pin positions, added connector for lights and power
2026-03-04 Updated Components
    Changed logic shifter circuit, added logic shifters for lights
2026-03-04 fixed misplaced file
2026-03-10 Update
    Changed logic shifters back to older version, changed names of outputs for clarification, added shifter for echo pin
2026-03-11 Fix after computer crash
2026-03-11 Edited power shut off components
    Placed diodes on gate of power shut off mosfet, one wired to esp32, other wired to keyed power detection
2026-03-12 Updated code
    Updated code to reflect current changes in schematic
2026-03-12 Fixed file location
2026-03-12 added servo attachments
2026-03-19 added note for voltage divider values
    added note for voltage divider values, r1=39k, r2=10k
2026-04-01 Update instrument_panel_code_esp32.ino
    Changed pot variables to sense.
    Added values for voltage divider code.
    Changed servo code to not use PCA chips.
    Added sensor calibration charts.
2026-04-02 file cleanup
2026-04-02 Added missing pin assignments
    Added pins for echo and trigger. Added pin for LED data. Deleted second speaker pin
2026-04-02 Fix errors
    Removed duplicate code. Fixed pin assignments
2026-04-02 Fixed pin assignments
2026-04-03 Update instrument_panel_code_esp32.ino
    Fixed errors, noted Volts function needs rewrite
2026-04-08 Added components
2026-04-08 fixed file locations
2026-04-08 updated pins/variables
    Removed fog light code. Changed pin names for clarity. Reassigned pin position for correct PWM output
2026-04-08 update to correct verison
2026-04-13 Initial Commit
    Created test files for the gauge face for 3D printing
2026-04-14 Started prototype PCB layout
2026-04-14 Update comments
    removed old code. added comments to functions that need to be written
2026-04-16 Added function templates
    Added templates for display, and fault detection functions. Deleted unused function. Added mileage variables
2026-05-11 pin update
    Updated pin assignments
2026-06-04 Update instrument_panel_code_esp32.ino
    Changed code to use rtos instead of super loop format
2026-06-23 added components
    Added additional components
2026-06-26 Update Schematic
    Reverted to older logic shifter design. Added single stage amplifier. Added voltage dividers for gauges.
2026-06-29 Update test bench.kicad_sch
    changed arduinos to esp32
